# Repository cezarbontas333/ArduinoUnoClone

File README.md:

# ArduinoUnoClone
PCB design of an Arduino Uno clone.

### Description
The clone was made in mind with the possibility of the board to be realised in a DYI fashion, there are few small SMD components which should be somewhat easily be soldered to the board. This design omits the inclusion of an on-board programmer, that need to be plugged into the connector annotated with J7. Power delivery is on a separate 2 pin connector (J5). Otherwise, this should function the same as any Arduino Uno board that is commercially available.

### Additional notes
This project was made with KiCad, project files included are the schematics and the PCB design.

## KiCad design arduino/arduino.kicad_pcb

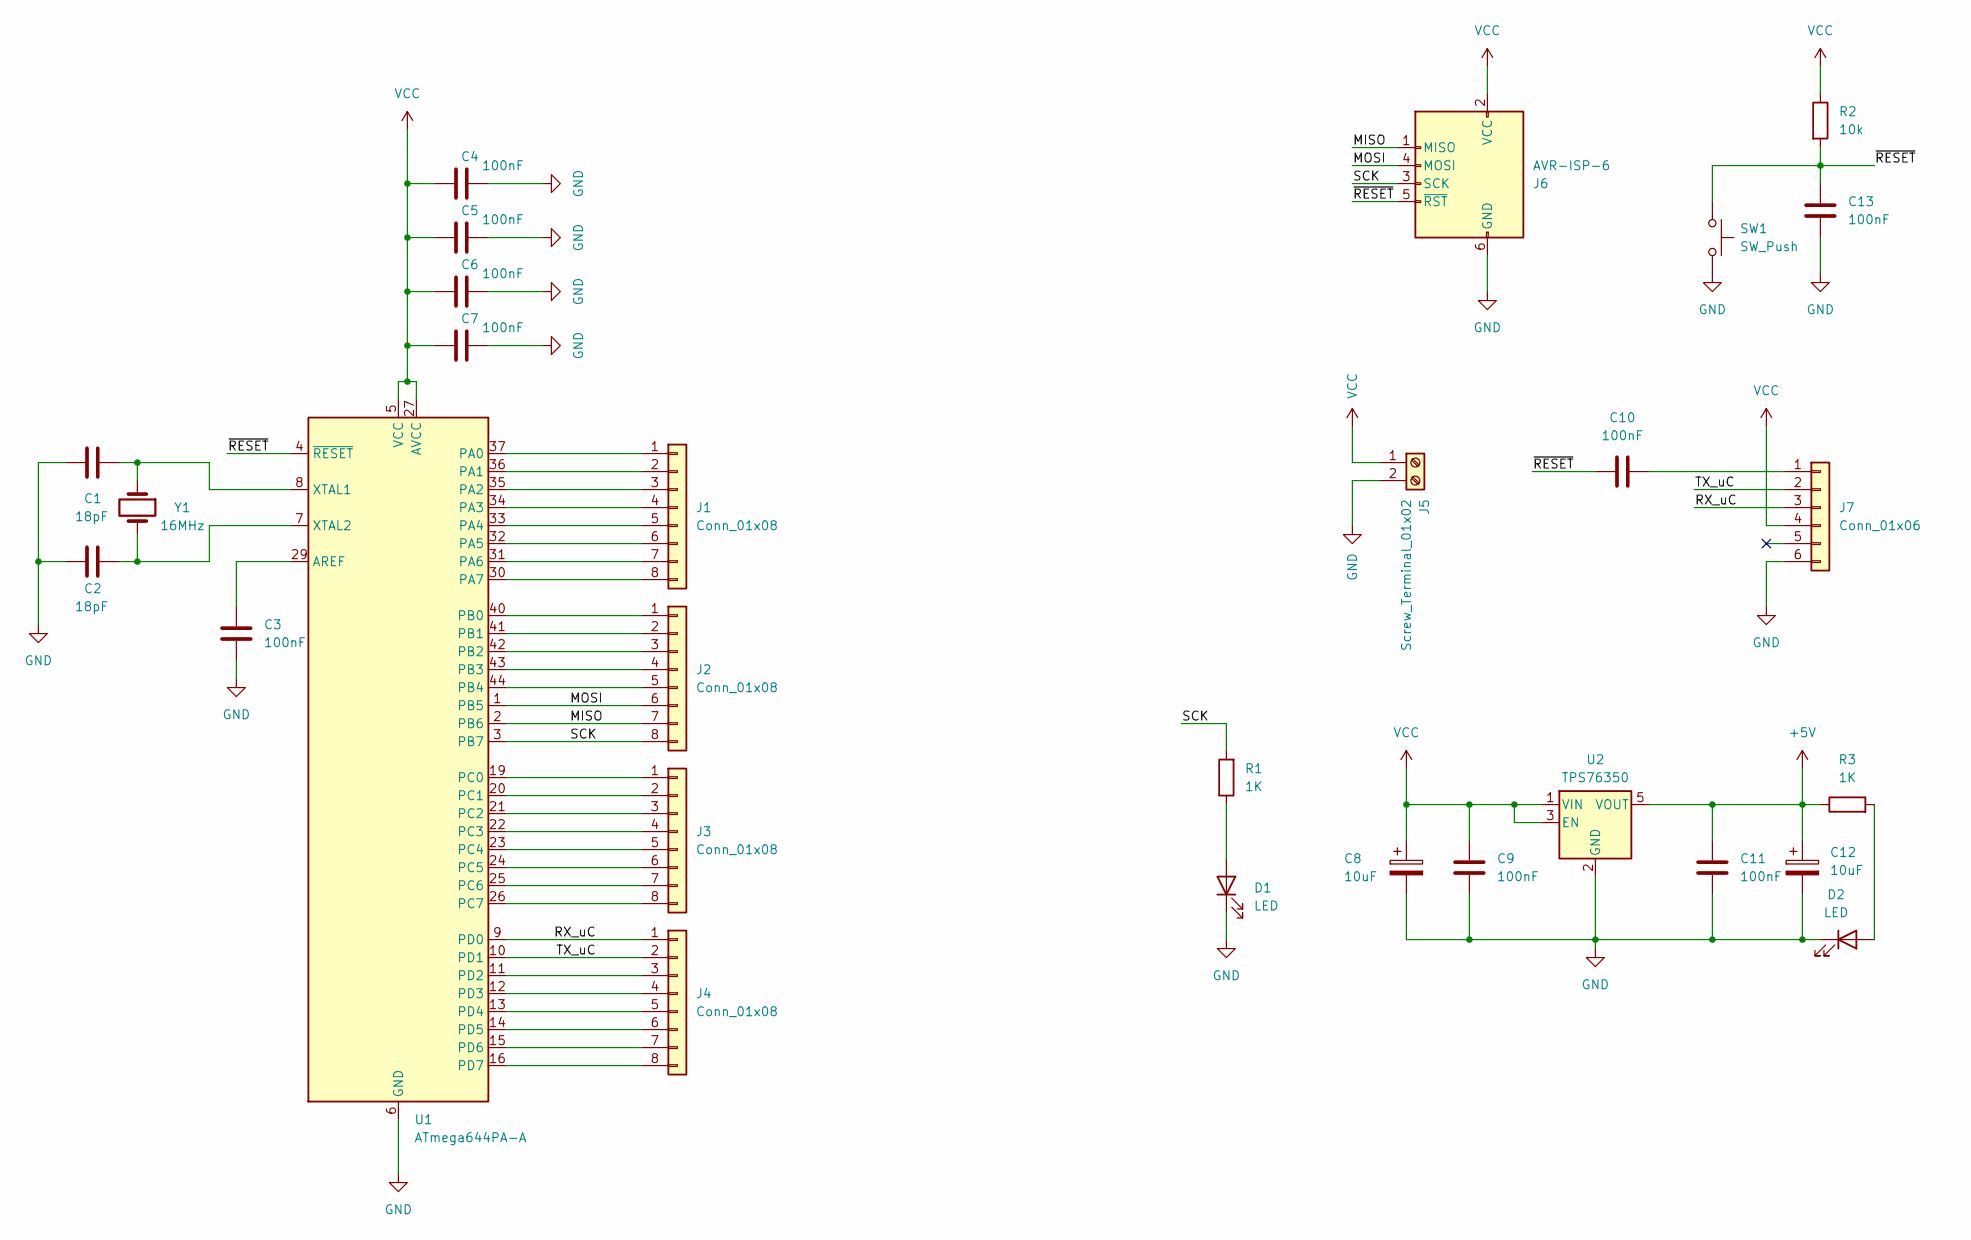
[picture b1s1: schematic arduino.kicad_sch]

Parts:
C1, C2: 18pF; C_0603_1608Metric_Pad1.08x0.95mm_HandSolder
C3, C4, C5, C6, C7, C9, C10, C11, C13: 100nF; C_0603_1608Metric_Pad1.08x0.95mm_HandSolder
C8, C12: 10uF; CP_Radial_D7.5mm_P2.50mm
D1, D2: LED; LED_D5.0mm
J1, J2, J3, J4: Conn_01x08; PinHeader_1x08_P2.54mm_Vertical
J5: Screw_Terminal_01x02; PhoenixContact_MCV_1,5_2-G-3.5_1x02_P3.50mm_Vertical
J6: AVR-ISP-6; IDC-Header_2x03_P2.54mm_Vertical
J7: Conn_01x06; PinHeader_1x06_P2.54mm_Vertical
R1, R3: 1K; R_Axial_DIN0204_L3.6mm_D1.6mm_P7.62mm_Horizontal
R2: 10k; R_Axial_DIN0204_L3.6mm_D1.6mm_P7.62mm_Horizontal
SW1: SW_Push; SW_PUSH_6mm
U1: ATmega644PA-A; TQFP-44_10x10mm_P0.8mm
U2: TPS76350; SOT-23-5
Y1: 16MHz; Crystal_HC49-4H_Vertical

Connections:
+5V: C11.1, C12.1, R3.1, U2.5 (VOUT)
/MISO: J2.7, J6.1 (MISO), U1.2 (PB6)
/MOSI: J2.6, J6.4 (MOSI), U1.1 (PB5)
/RX_uC: J4.1, J7.3, U1.9 (PD0)
/SCK: J2.8, J6.3 (SCK), R1.2, U1.3 (PB7)
/TX_uC: J4.2, J7.2, U1.10 (PD1)
/~RESET: C10.1, C13.1, J6.5 (~RST), R2.2, SW1.1, U1.4 (~RESET)
GND: C1.2, C2.2, C3.2, C4.2, C5.2, C6.2, C7.2, C8.2, C9.2, C11.2, C12.2, C13.2, D1.1 (K), D2.1 (K), J5.2, J6.6 (GND), J7.6, SW1.2, U1.6 (GND), U1.18 (GND), U1.28 (GND), U1.39 (GND), U2.2 (GND)
unnamed: D1.2 (A), R1.1
unnamed: D2.2 (A), R3.2
unnamed: J1.1, U1.37 (PA0)
unnamed: J1.2, U1.36 (PA1)
unnamed: J1.3, U1.35 (PA2)
unnamed: J1.4, U1.34 (PA3)
unnamed: J1.5, U1.33 (PA4)
unnamed: J1.6, U1.32 (PA5)
unnamed: J1.7, U1.31 (PA6)
unnamed: J1.8, U1.30 (PA7)
unnamed: J2.1, U1.40 (PB0)
unnamed: J2.2, U1.41 (PB1)
unnamed: J2.3, U1.42 (PB2)
unnamed: J2.4, U1.43 (PB3)
unnamed: J2.5, U1.44 (PB4)
unnamed: J3.1, U1.19 (PC0)
unnamed: J3.2, U1.20 (PC1)
unnamed: J3.3, U1.21 (PC2)
unnamed: J3.4, U1.22 (PC3)
unnamed: J3.5, U1.23 (PC4)
unnamed: J3.6, U1.24 (PC5)
unnamed: J3.7, U1.25 (PC6)
unnamed: J3.8, U1.26 (PC7)
unnamed: J4.3, U1.11 (PD2)
unnamed: J4.4, U1.12 (PD3)
unnamed: J4.5, U1.13 (PD4)
unnamed: J4.6, U1.14 (PD5)
unnamed: J4.7, U1.15 (PD6)
unnamed: J4.8, U1.16 (PD7)
unnamed: C10.2, J7.1
unnamed: C3.1, U1.29 (AREF)
unnamed: C1.1, U1.8 (XTAL1), Y1.1
unnamed: C2.1, U1.7 (XTAL2), Y1.2
VCC: C4.1, C5.1, C6.1, C7.1, C8.1, C9.1, J5.1, J6.2 (VCC), J7.4, R2.1, U1.5 (VCC), U1.17 (VCC), U1.27 (AVCC), U1.38 (VCC), U2.1 (VIN), U2.3 (EN)

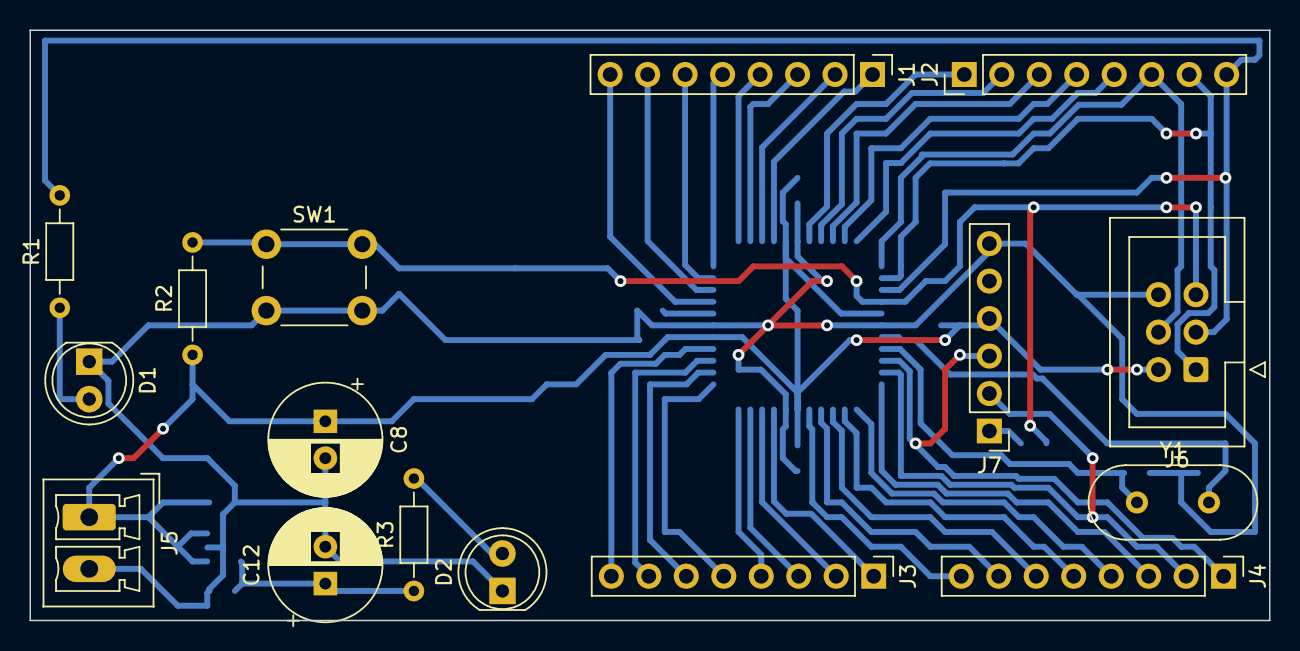
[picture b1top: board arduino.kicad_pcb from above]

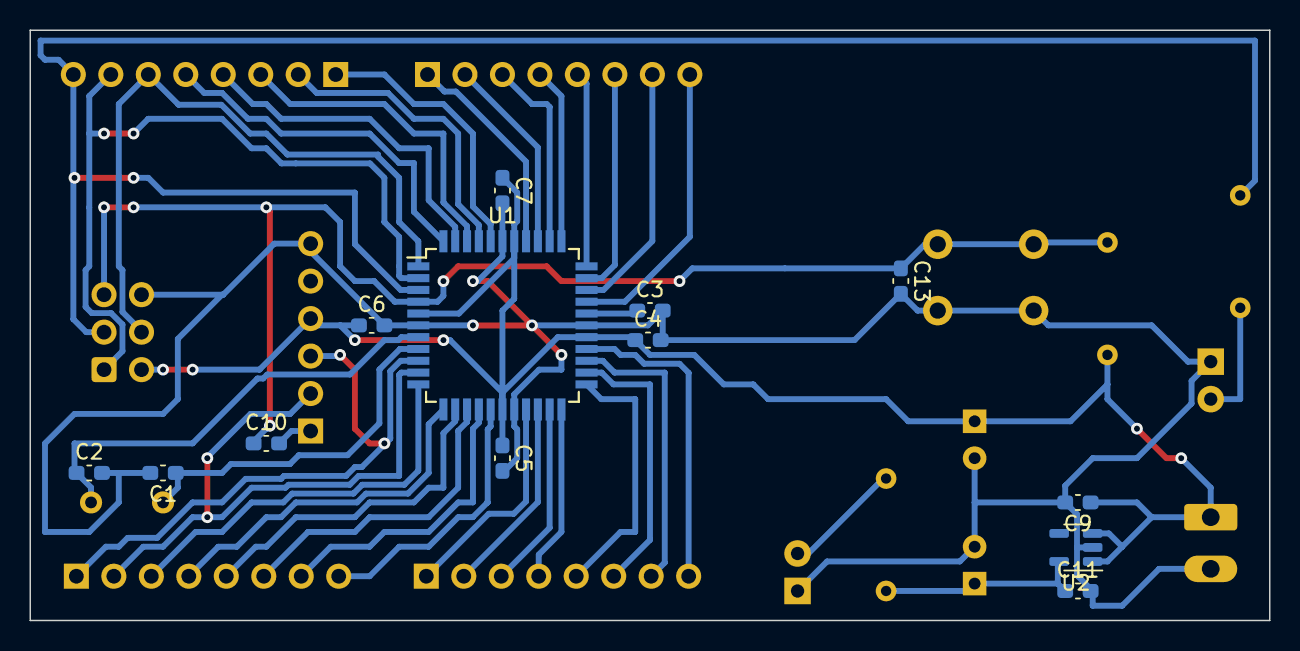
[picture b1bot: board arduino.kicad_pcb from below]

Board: 2 copper layers, 84.0 x 40.0 mm, 29 parts (13 on the bottom side), 42 nets.

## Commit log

2024-03-13 Initial (and probably final) design
